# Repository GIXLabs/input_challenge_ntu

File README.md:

# Challenge
You are tasked with creating a hardware device to play [Tetris in the browser](https://tetris.com/play-tetris). We have provided some pre-programmed boards that handle most of the electronics and coding, but you will need to build the physical interface.

You must choose a target user and scenario for whom you're making your device.

# Table of Contents
- [Procedure](#procedure)
- [Materials](#materials)
- [Electrical Assembly](#electrical-assembly)
- [Code](src/)
- [Mechanical Design](cad/)
- [Extra Credit](#extra-credit)

# Procedure
1. [Assemble the electronics](#electrical-assembly) and see how they work with Tetris. Try playing it on a computer and make sure you get the button presses you expect, but don't feel the need to edit the code at this point. See the table in the [Operation section](#operation) for what the buttons are supposed to do.
    1. You may find that your computer behaves funny when you plug the device in. The device is trying to press the down arrow regularly, but you can turn that off by either turning the potentiometer all the way down or by disconnecting the potentiometer.
1. Come up with a target user and scenario for whom you're making your device. Spend about 10 minutes coming up with this.
1. Build the enclosure using the tools in the Prototyping Lab. Cardboard and hot glue is perfectly fine, but feel free to stretch a little and try [using the lasers](cad/README.md) or any other tool in the main area. Making a basic lasercut enclosure only takes about 20 minutes, even with no experience.
1. Test your prototype, in other words, [play Tetris](https://tetris.com/play-tetris).
1. Make your prototype better based on your test. Consider trying out one of the challenges in the [Extra Credit](#extra-credit) section.

# Materials

- Raspberry Pi Pico main board (yours will have less green blocks)
- Micro USB cable (not pictured)
- Switches
- Potentiometer
- Anything you can find in the Prototyping Lab

# Electrical Assembly
The button wires go into the green terminal blocks with two holes. It does not matter which end goes into which hole since these buttons are not polarized. You will need to depress the square on the top of the green terminal block to let the wire slip in.

The potentiometer wires go into the green terminal blocks with three holes. The black wire needs to go into the center hole, but the other two can be placed in either side hole (but not the same one!).

# Operation

| Pin | Keystroke |
| --- | --- |
| GP2 | Left Button |
| GP3 | Right Button |
| GP4 | Up Button (rotate the piece) |
| GP5 | Spacebar (drop the piece)* |

*The code loaded on the device does not implement the spacebar button. For information on editing the code, [click here](src/). To achieve high scores, you'll need that functionality.

The potentiometer (knob) controls how fast bricks fall by "feathering" the down button. If the potentiometer is not wired, this feature will be deactivated.

# Extra Credit
- Fabrication
    - Lasercut and heat bend a controller.
    - 3D print your controller. (very hard, but doable with the faster printers)
- Electronics
    - Find a different button to use with the board in the Prototyping Lab.
    - Use something other than a real button as a button.
- Coding
    - Implement the spacebar code.
    - Implement a series of commands instead of just one button press. For example, pressing the button connected to GP4 could send several rotation commands instead of one.
    - Edit the potentiometer code to have the blocks fall faster or slower.

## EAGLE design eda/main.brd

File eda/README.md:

# Schematic

# Buttons
Each button is wired between a digital pin on the Pico and ground, making it active Low and working well with the internal pull-up resistors. This means that when the button is pressed, the pin reads 0V (also known as Ground, Low, and False). When the button is released, the internal pull-up resistors pull the pin to 3.3V (also known as VCC, High, and True). The pull-up resistors ensure that the pin is pulled to a known state when not pressed.

The wires are the same color because switches can be wired up in either direction and still work. In other words, they are not polarized components. Just make sure that two wires coming from the buttons go to different ports on the same terminal block.

# Knobs
Each potentiometer has 3 wires: power, signal, and ground. The signal pin is tied to one of the analog pins on the Pico. 

A potentiometer is basically one long resistor with a third connection somewhere in the middle of the resistor. By turning the knob, you change where that third connection is made, changing the resistance on either side of the third connection. Note: the overall resistance does not change, just how that resistance is distributed. This change in the position of the third connection results in a change in voltage, which the Pico can read on an analog pin.

That change in voltage is converted to something in the code.

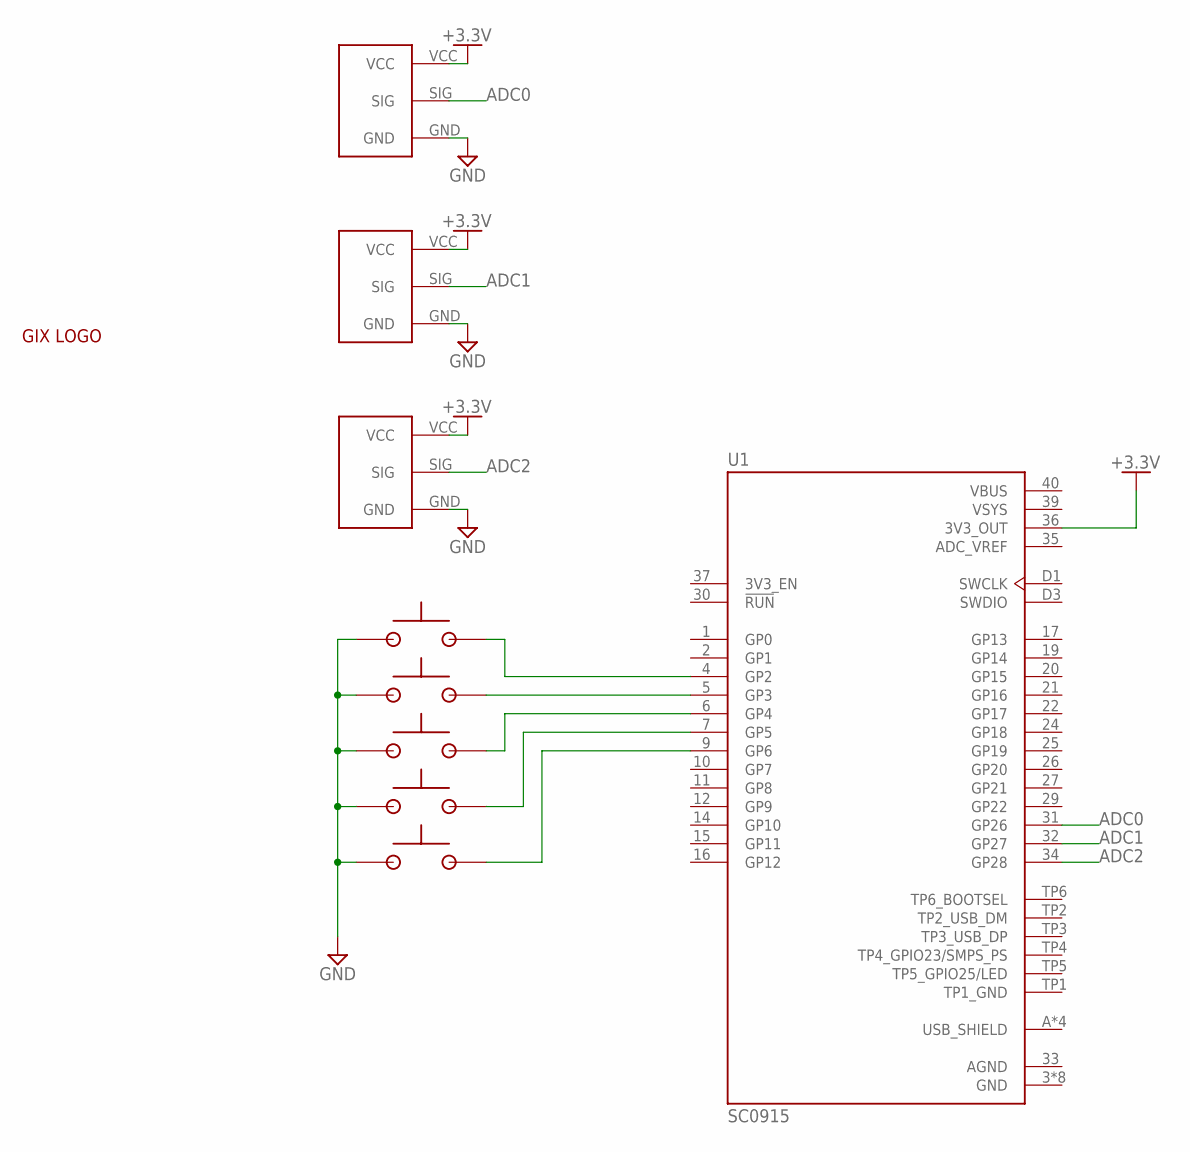
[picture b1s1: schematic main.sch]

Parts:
U1: SC0915; MODULE_SC0915
U$1, U$2, U$3, U$4, U$5: TERMINAL_BLOCK
U$6, U$7, U$8: 3PIN_SENSOR; TERMINAL_BLOCK_3P
U$9: LOGO

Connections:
+3.3V: U1.36 (3V3_OUT), U$6.VCC, U$7.VCC, U$8.VCC
ADC0: U1.31 (GP26), U$6.SIG
ADC1: U1.32 (GP27), U$7.SIG
ADC2: U1.34 (GP28), U$8.SIG
ADC_VREF: U1.35 (ADC_VREF)
AGND: U1.33 (AGND)
GND: U1.3 (GND), U1.8 (GND), U1.13 (GND), U1.18 (GND), U1.23 (GND), U1.28 (GND), U1.38 (GND), U1.D2 (GND), U$1.P$1, U$2.P$1, U$3.P$1, U$4.P$1, U$5.P$1, U$6.GND, U$7.GND, U$8.GND
unnamed: U1.6 (GP4), U$3.P$2
unnamed: U1.5 (GP3), U$2.P$2
unnamed: U1.4 (GP2), U$1.P$2
unnamed: U1.7 (GP5), U$4.P$2
unnamed: U1.9 (GP6), U$5.P$2
TP1_GND: U1.TP1 (TP1_GND)
USB_SHIELD: U1.A (USB_SHIELD), U1.B (USB_SHIELD), U1.C (USB_SHIELD), U1.D (USB_SHIELD)
VBUS: U1.40 (VBUS)
VSYS: U1.39 (VSYS)

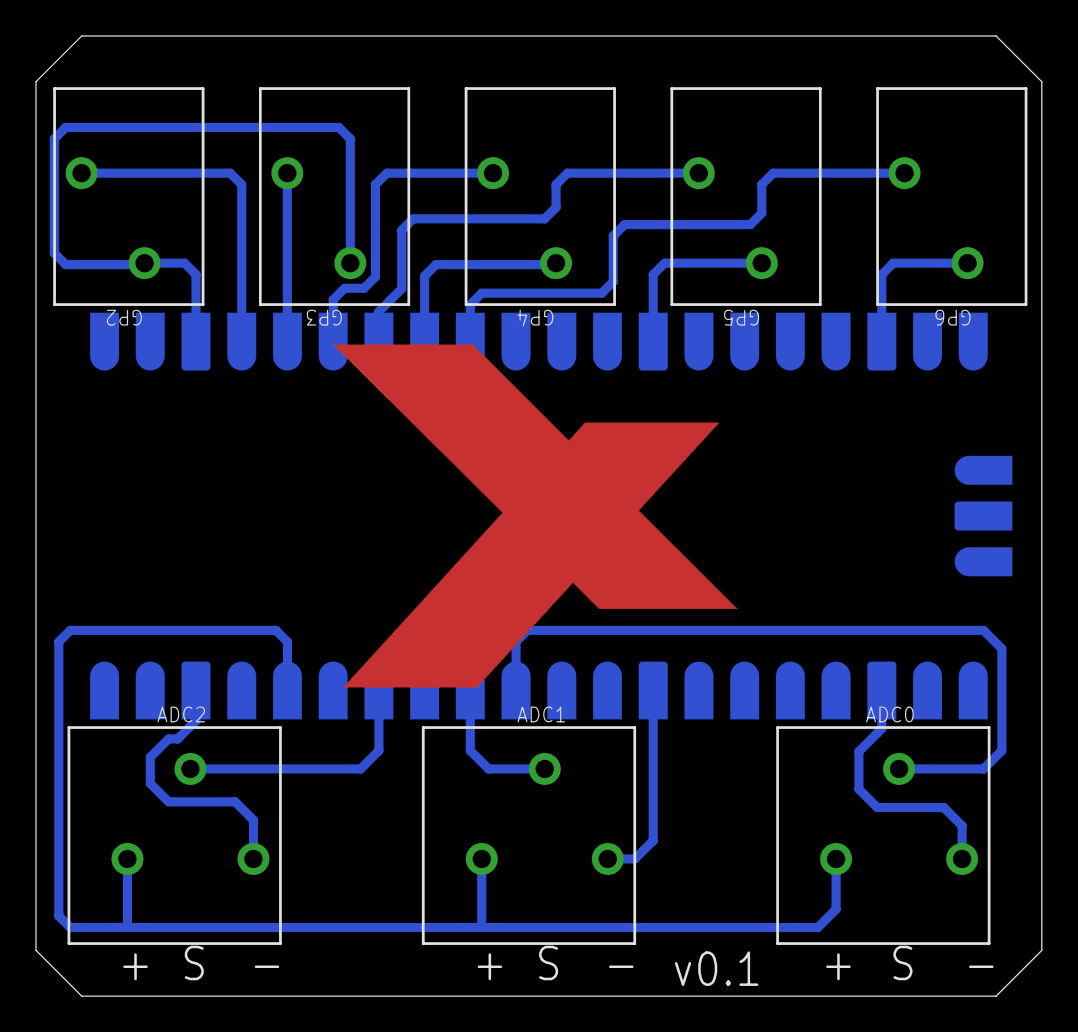
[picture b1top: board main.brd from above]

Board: 2 copper layers, 55.9 x 53.3 mm, 10 parts (1 on the bottom side), 11 nets.

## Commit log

2023-03-13 Initial commit. Needs code. 3 terminal block needs updating and board needs rerouting.
2023-03-21 Modified board to reflect fixed 3 pos footprint.
2023-03-24 Added text for electrical assembly and placeholders for the images.
2023-03-24 Added information on required libraries for code. Added links in main table of contents.
2023-03-24 Whoops, forgot the main README, which has the table of contents edits previously mentioned.
2023-03-28 Added single button example code.
2023-03-28 Added gif of using terminal blocks.
2023-03-28 Added potentiometer wiring image.
2023-03-29 Added picture showing layout of components. Still needs labels.
2023-03-29 Added mapping table from buttons to keystrokes. Cleaned up the prompt. Removed schematics from table of contents.
2023-03-29 Added link to keycode list in src README
2023-03-30 Added potentiometer example.
2023-03-30 Added basic main code file. Still needs other buttons implemented.
2023-03-30 Updated main code. Changed the button list to a list of dictionaries to reduce spaghetti.
2023-03-30 Fixed fatal syntax error in dictionary assignment.
2023-04-04 Added code with intentional lack of functionality to be initially flashed to the boards.
2023-04-04 Added extra credit section.
2023-04-04 Added Getting Started section.
2023-04-05 Added CAD models for the carrier.
2023-04-05 Added link to CAD models in main README.md
2023-04-05 Added more information on programming the boards.
2023-04-05 Changed order of Extra Credit options.
2023-04-05 Added links to lasercutting tutorial.
2023-04-05 Edited values on potentiometer detection algorithm to make it more reliable.
2023-04-06 Added more links to the Tetris game in the Procedure section (previously called Getting Started).
2023-04-06 Added line about the down key issue to the Procedure section.
2023-04-06 Added coment about the amount of terminal blocks on the main board.
2024-03-11 reformatted the code
2024-03-14 additional abstraction of functionality
2024-03-29 Added svgs for different holes.
2024-04-01 Added lots of details about the lasering process. To Do: Add images of Glowforge interface.
2024-04-01 Added images for Glowforge interface.
2024-04-01 Added links to lasercutting tutorial from main page.
2024-04-02 Fixed some links, added note about Glowforge account.
2024-04-02 Added more detail about greyed out parts, finding material, and changed order of items.
2024-04-02 Added clarification to material placement, finger size, and Glowforge number.
2024-04-02 Changed MDF to Birch.
2024-04-04 Fixed some bugs with potentiometer by adding more checks.
2024-04-04 Removed s from Labs
2024-04-04 Fixed type in potentiometer wiring section.
2024-04-04 Added corrected link for keycodes.
2025-07-11 Added files for generic rectangles and circles.
2025-07-11 Added links to circle and rectangle.
2025-07-12 Fixed glowforge add interface.
2025-07-15 Changed cherry plywood to general laser material.
